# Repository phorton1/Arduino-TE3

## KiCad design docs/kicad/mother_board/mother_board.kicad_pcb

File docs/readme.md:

## TE3 - teensyExpression3

### Please see the [teensyExpression3 documentation](https://phorton1.github.io/Arduino-TE3/)

### License

This program is free software: you can redistribute it and/or modify
it under the terms of the GNU General Public License Version 3 as published by
the Free Software Foundation.

This program is distributed in the hope that it will be useful,
but WITHOUT ANY WARRANTY; without even the implied warranty of
MERCHANTABILITY or FITNESS FOR A PARTICULAR PURPOSE.  See the
GNU General Public License for more details.

Please see **LICENSE.TXT** for more information.

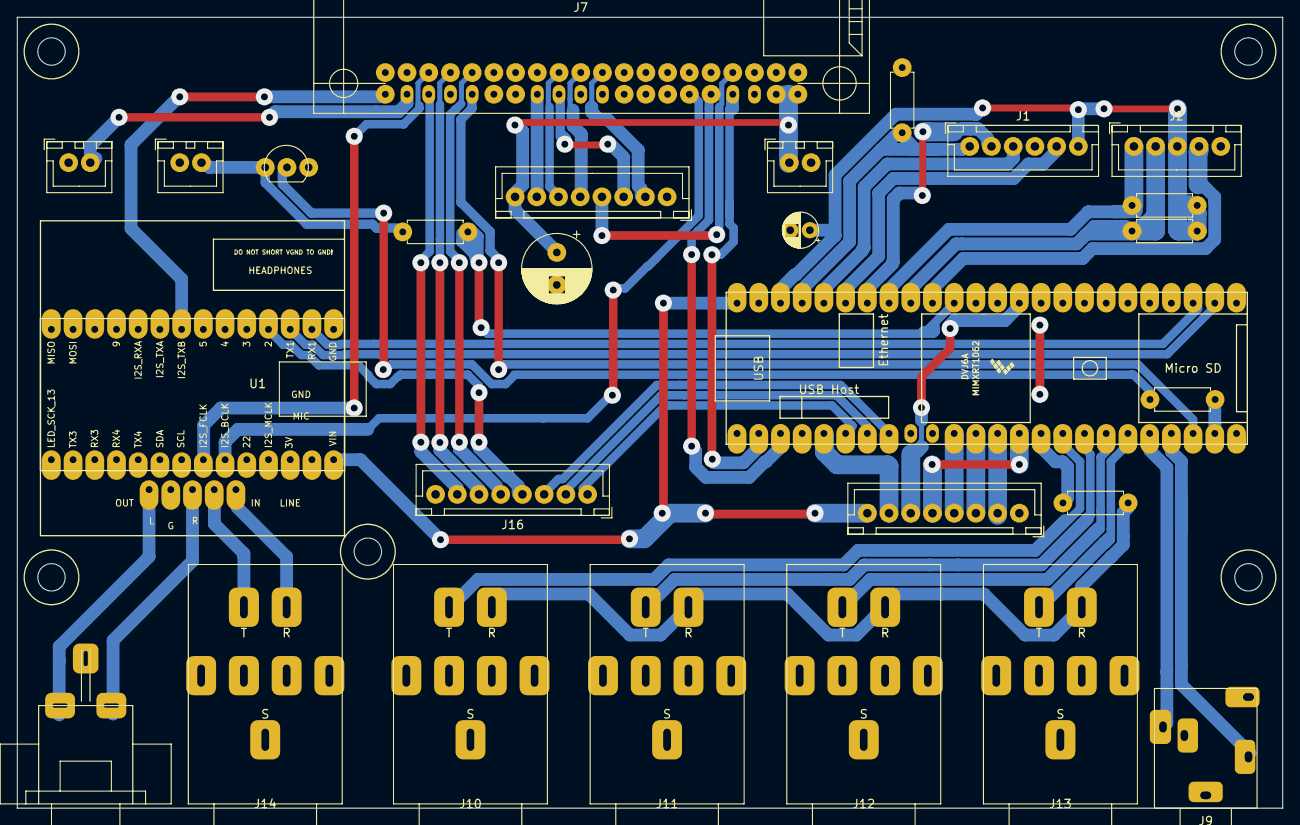
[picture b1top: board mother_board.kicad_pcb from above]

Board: 2 copper layers, 148.0 x 92.5 mm, 27 parts (0 on the bottom side), 54 nets.

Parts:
C1: 100uf; CP_my100uf
C2: 47uf; CP_my10uf
J1: ROW_BOARDS; myJSTx06
J2: ROTARIES; myJSTx05
J3: TE_DISPLAY; myJSTx08
J4: RPI_DISPLAY; myJSTx08
J5: rPi_5V; myJSTx02
J6: RPI_RUN; myJSTx02
J7: rpi_connector; rpi_zero_2w_for_TE3
J8: I2S_TXB; myJSTx02
J9: EigthInchJack1
J10: PEDAL1; QuarterInchJack1
J11: PEDAL2; QuarterInchJack1
J12: PEDAL3; QuarterInchJack1
J13: PEDAL4; QuarterInchJack1
J14: GUITAR_IN; QuarterInchJack1
J15: LINE_OUT; RCA2_PCB_milled
J16: LEDS; myJSTx08
Q1: BC547; myTransistor
R1, R2, R4: 1K; myResistor
R3, R5: 220; myResistor
R11: 10K; myResistor
U1: teensyAudioRevD_WithAudio; audioShieldRevD_audioPinsStack
U2: myTeensy4.1; teensy41

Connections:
+5V: J3.8, U1.28, U2.48
BTN_CLK: J1.5, U2.43
BTN_DIN: J1.3, U2.44
BTN_SENSE: J1.1, R11.1, U2.45
GND: C1.2, C2.2, J1.4, J2.5, J3.1, J4.1, J5.2, J6.1, J7.6, J7.9, J7.14, J7.20, J7.25, J7.30, J7.34, J7.39, J8.1, J9.S, J10.S, J11.S, J12.S, J13.S, J14.S, J15.G, J16.8, Q1.3, R11.2, U1.1, U1.27, U1.32, U2.1, U2.34, U2.47
I2S_BCLK: J7.12, U1.23
I2S_FCLK: J7.35, U1.22
I2S_RXB: J7.40, U1.8
I2S_TXB: J7.38, J8.2
LED_AUDIO_BUSY: J16.4, U1.4
LED_DIN: J1.2, U2.42
LED_RPI_BUSY: J7.31, J16.5
LED_RPI_I2S_RX: J7.33, J16.6
LED_RPI_I2S_TX: J7.36, J16.7
LED_RPI_READY: J16.3, U2.8
LED_RPI_RUN: J16.2, U2.7
LED_T3_BUSY: J16.1, U2.6
LINE_IN_L: J14.R, U1.29
LINE_IN_R: J14.T, U1.30
LINE_OUT_L: J15.L, U1.33
LINE_OUT_R: J15.R, U1.31
unnamed: J10.R, J11.R, J12.R, J13.R, R5.2
unnamed: Q1.2, R4.2
PEDAL1: J10.T, U2.16
PEDAL2: J11.T, U2.17
PEDAL3: J12.T, U2.18
PEDAL4: J13.T, U2.19
PI_REBOOT: R4.1, U2.23
ROT_INT: J2.4, U2.39
RPI_5V: C1.1, J4.8, J5.1, J7.2, J7.4
RPI_LCD_CS: J4.3, J7.24
RPI_LCD_DC: J4.4, J7.7
RPI_MISO: J4.5, J7.21
RPI_MOSI: J4.2, J7.19
RPI_READY: J7.32, U2.22
RPI_RUN: J6.2, Q1.1, R3.2
RPI_SCLK: J4.6, J7.23
RPI_T_CS: J4.7, J7.26
SENS_PI_RUN: R3.1, U2.38
T41_3V3: C2.1, J1.6, J2.3, R1.1, R2.1, R5.1, U2.15, U2.46
T41_LCD_CS: J3.3, U2.12
T41_LCD_DC: J3.4, U2.11
T41_MISO: J3.5, U2.14
T41_MOSI: J3.2, U2.13
T41_RX1: J7.8, U2.2
T41_RX7: J9.T, U2.21
T41_RX8: U1.3, U2.26
T41_SCL: J2.1, R1.2, U2.41
T41_SCLK: J3.6, U2.35
T41_SDA: J2.2, R2.2, U2.40
T41_TX1: J7.10, U2.3
T41_TX7: J9.R, U2.20
T41_TX8: U1.2, U2.27
T41_T_CS: J3.7, U2.5

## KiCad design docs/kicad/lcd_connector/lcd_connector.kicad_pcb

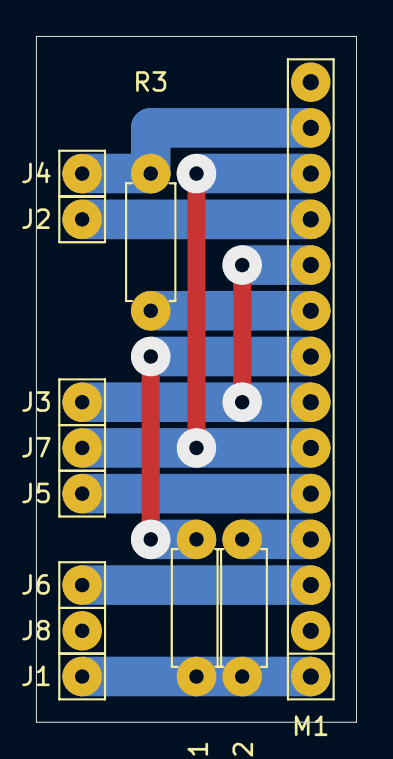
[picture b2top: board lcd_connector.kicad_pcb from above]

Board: 2 copper layers, 17.8 x 38.1 mm, 12 parts (0 on the bottom side), 11 nets.

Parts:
J1: 5V; my1pin
J2: T_CS; my1pin
J3: CLK; my1pin
J4: MISO; my1pin
J5: DC; my1pin
J6: CS; my1pin
J7: MOSI; my1pin
J8: GND; my1pin
M1: TFT_ILI9488; myPinSocket_1x14
R1: 100; myResistor
R2: 10K; myResistor
R3: 220; myResistor

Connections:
unnamed: J1.1, M1.1, R1.1, R2.1
unnamed: J2.1, M1.11
unnamed: J3.1, M1.7, M1.10
unnamed: J4.1, M1.13, R3.1
unnamed: J5.1, M1.5
unnamed: J6.1, M1.3
unnamed: J7.1, M1.6, M1.12
unnamed: J8.1, M1.2
unnamed: M1.4, R2.2
unnamed: M1.8, R1.2
unnamed: M1.9, R3.2

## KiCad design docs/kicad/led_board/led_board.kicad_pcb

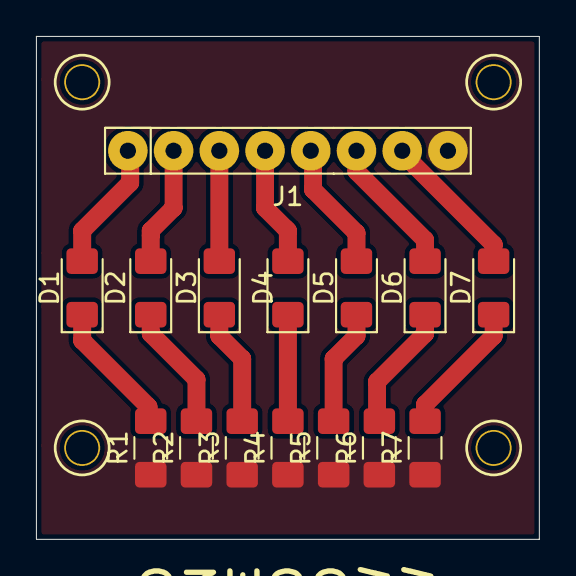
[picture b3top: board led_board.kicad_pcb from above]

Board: 2 copper layers, 27.9 x 27.9 mm, 15 parts (0 on the bottom side), 15 nets.

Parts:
D1, D2, D3, D4, D5, D6, D7: LED_Small; D_1206_3216Metric_Pad1.42x1.75mm_HandSolder
J1: Conn_01x08; my8Pin
R1, R2, R3, R4, R5, R6, R7: R_Small; R_1206_3216Metric_Pad1.42x1.75mm_HandSolder

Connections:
GND: J1.8, R1.1, R2.1, R3.1, R4.1, R5.1, R6.1, R7.1
unnamed: D1.1, R1.2
unnamed: D1.2, J1.1
unnamed: D2.1, R2.2
unnamed: D2.2, J1.2
unnamed: D3.1, R3.2
unnamed: D3.2, J1.3
unnamed: D4.1, R4.2
unnamed: D4.2, J1.4
unnamed: D5.1, R5.2
unnamed: D5.2, J1.5
unnamed: D6.1, R6.2
unnamed: D6.2, J1.6
unnamed: D7.1, R7.2
unnamed: D7.2, J1.7

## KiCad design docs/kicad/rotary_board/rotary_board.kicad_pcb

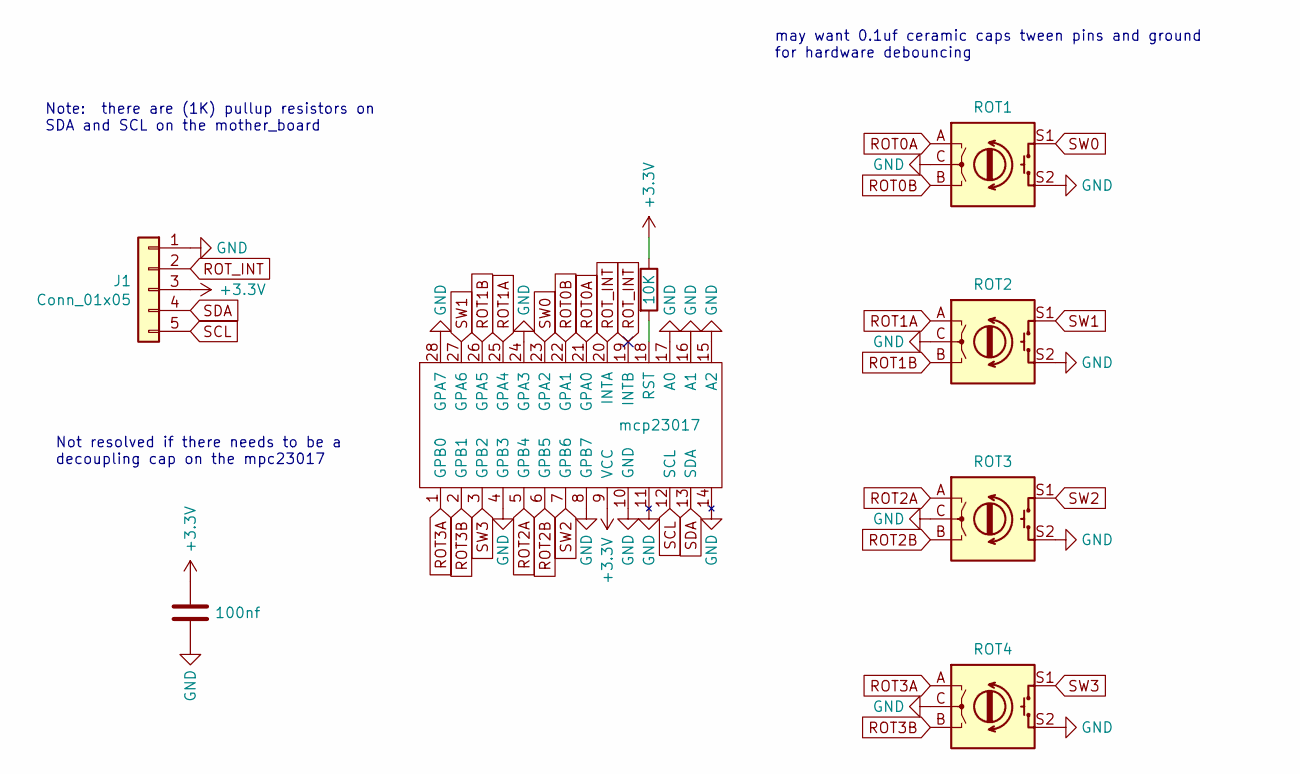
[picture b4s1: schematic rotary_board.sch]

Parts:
C1: 100nf; myCapCeramicSmall
J1: Conn_01x05; my5Pin
R1: 10K; myResistor
SW1: ROT1; myRotaryEncoder
SW2: ROT2; myRotaryEncoder
SW3: ROT3; myRotaryEncoder
SW4: ROT4; myRotaryEncoder
U1: mcp23017; myDip28

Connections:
+3V3: C1.1, J1.3, R1.1, U1.9 (VCC)
GND: C1.2, J1.1, SW1.C, SW1.S2, SW2.C, SW2.S2, SW3.C, SW3.S2, SW4.C, SW4.S2, U1.4 (GPB3), U1.8 (GPB7), U1.10 (GND), U1.11, U1.14, U1.15 (A2), U1.16 (A1), U1.17 (A0), U1.24 (GPA3), U1.28 (GPA7)
unnamed: R1.2, U1.18 (RST)
ROT0A: SW1.A, U1.21 (GPA0)
ROT0B: SW1.B, U1.22 (GPA1)
ROT1A: SW2.A, U1.25 (GPA4)
ROT1B: SW2.B, U1.26 (GPA5)
ROT2A: SW3.A, U1.5 (GPB4)
ROT2B: SW3.B, U1.6 (GPB5)
ROT3A: SW4.A, U1.1 (GPB0)
ROT3B: SW4.B, U1.2 (GPB1)
ROT_INT: J1.2, U1.19 (INTB), U1.20 (INTA)
SCL: J1.5, U1.12 (SCL)
SDA: J1.4, U1.13 (SDA)
SW0: SW1.S1, U1.23 (GPA2)
SW1: SW2.S1, U1.27 (GPA6)
SW2: SW3.S1, U1.7 (GPB6)
SW3: SW4.S1, U1.3 (GPB2)

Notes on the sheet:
Note: there are (1K) pullup resistors on SDA and SCL on the mother_board
Not resolved if there needs to be a decoupling cap on the mpc23017
may want 0.1uf ceramic caps tween pins and ground for hardware debouncing

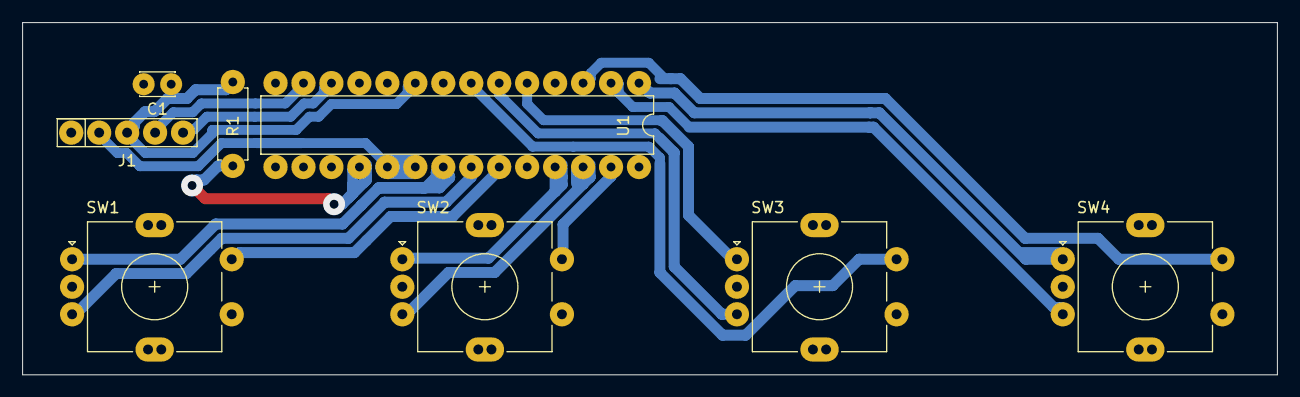
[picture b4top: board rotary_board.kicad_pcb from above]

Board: 2 copper layers, 114.0 x 32.0 mm, 8 parts (0 on the bottom side), 18 nets.

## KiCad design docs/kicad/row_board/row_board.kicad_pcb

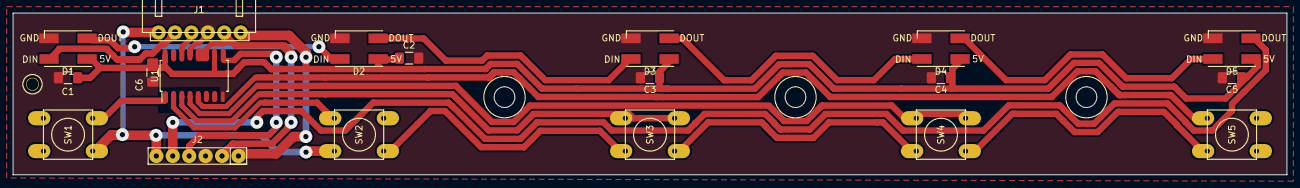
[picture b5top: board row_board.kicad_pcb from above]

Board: 2 copper layers, 197.0 x 25.0 mm, 19 parts (0 on the bottom side), 17 nets.

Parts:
C1, C2, C3, C4, C5: 100nf; C_1206_3216Metric_Pad1.42x1.75mm_HandSolder
C6: 10uf; C_1206_3216Metric_Pad1.42x1.75mm_HandSolder
D1, D2, D3, D4, D5: WS2812B; myWS2812
J1: Conn_01x06; invRightAngleJSTx06
J2: Conn_01x06; my6Pin-08mm
SW1, SW2, SW3, SW4, SW5: SW1; mySwitchSoft
U1: 74HC595; SOIC-16_4.55x10.3mm_P1.27mm

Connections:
+5V: C1.1, C2.1, C3.1, C4.1, C5.1, C6.1, D1.1, D2.1, D3.1, D4.1, D5.1, J1.6, J2.1, U1.10, U1.16
BTN_CLK: J1.5, J2.2, U1.11, U1.12
BTN_DIN: J1.3, U1.14
BTN_DOUT: J2.4, U1.9
BTN_SENSE: J1.1, J2.6, SW1.2, SW2.2, SW3.2, SW4.2, SW5.2
GND: C1.2, C2.2, C3.2, C4.2, C5.2, C6.2, D1.3, D2.3, D3.3, D4.3, D5.3, J1.4, J2.3, U1.8, U1.13
LED_DIN: D1.4, J1.2
LED_DOUT: D5.2, J2.5
unnamed: D1.2, D2.4
unnamed: D2.2, D3.4
unnamed: D3.2, D4.4
unnamed: D4.2, D5.4
unnamed: SW1.1, U1.1
unnamed: SW2.1, U1.2
unnamed: SW3.1, U1.3
unnamed: SW4.1, U1.4
unnamed: SW5.1, U1.5

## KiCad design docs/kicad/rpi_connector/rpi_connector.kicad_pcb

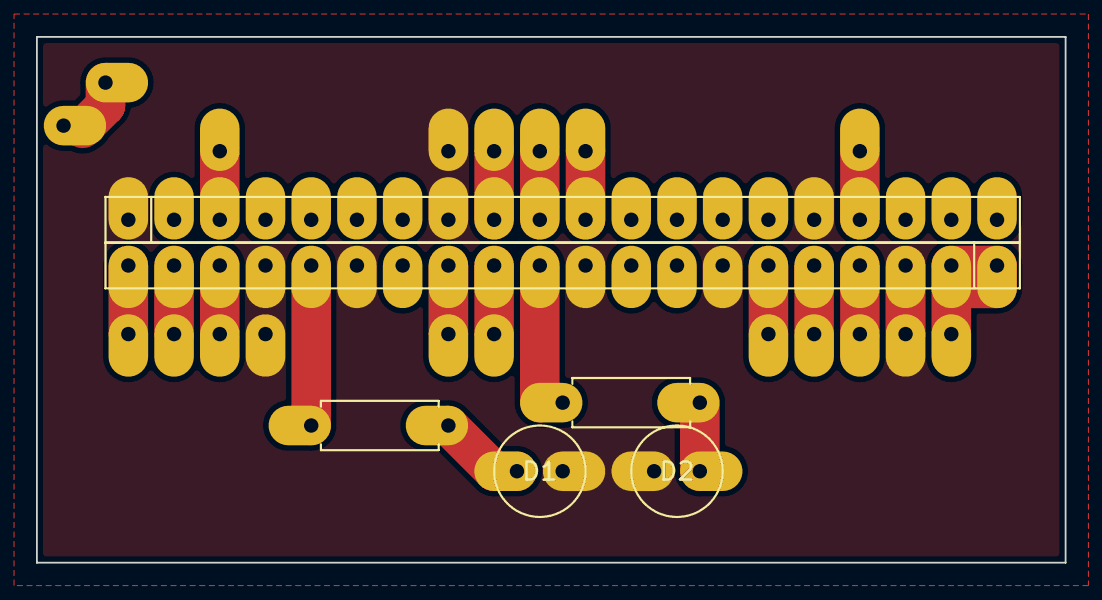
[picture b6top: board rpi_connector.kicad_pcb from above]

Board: 2 copper layers, 57.2 x 29.2 mm, 7 parts (0 on the bottom side), 6 nets.

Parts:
D1, D2: yellow; led_yellow
J12: RPI_RUN; Oval1Pin
J13: rpiB; pinSocket1x20_bottom
J14: rpiA; pinSocket1x20_bottom
R1, R2: 220; resistor

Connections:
GND: D1.1, D2.1, J13.1, J13.8, J13.16, J14.3, J14.7, J14.10, J14.15, J14.17
unnamed: D1.2, R1.1
unnamed: D2.2, R2.1
RPI_5V: J14.1, J14.2
RPI_I2S_RX_ACTIVE: J14.11, R2.2
RPI_I2S_TX_ACTIVE: J14.16, R1.2

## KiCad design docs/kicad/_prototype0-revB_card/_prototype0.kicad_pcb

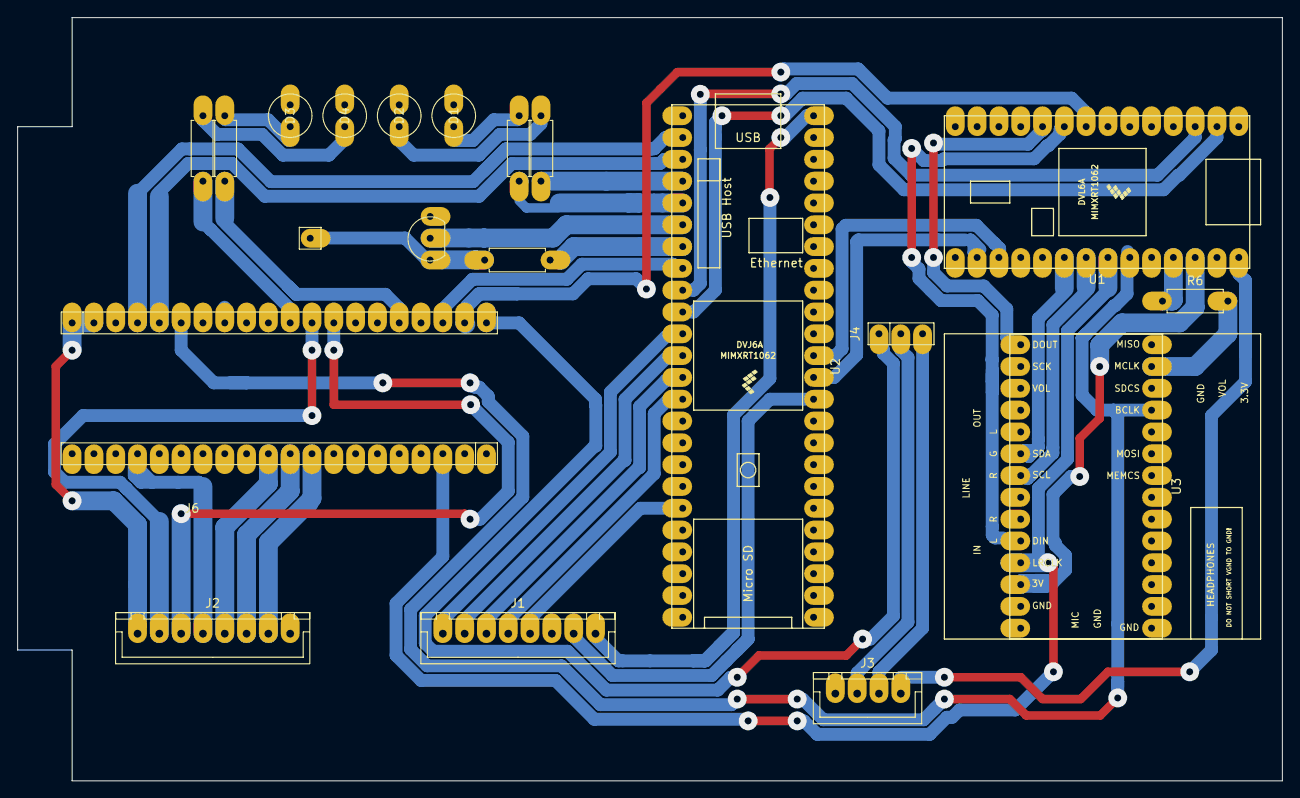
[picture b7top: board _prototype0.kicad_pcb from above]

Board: 2 copper layers, 147.3 x 88.9 mm, 21 parts (0 on the bottom side), 47 nets.

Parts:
D1: GREEN; led_green
D2: BLUE; led_blue
D3, D4: YELLOW; led_yellow
J1: T3_ILI9488; JST8
J2: RPI_ILI9488; JST8
J3: USB Host; JST4
J4: 40 bottom; pinSocket1x3
J5: RPI_RUN; pinSocket1x1
J6: rpiB; pinSocket1x20
J7: rpiA; pinSocket1x20
Q1: BC547; transistor
R1, R3, R4, R5: 220; resistor
R2: 560; resistor
R6: 100; resistor
U1: myTeensy4.0; teensy40
U2: myTeensy4.1; teensy41
U3: teensyAudioRevB; audioShieldRevB

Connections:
GND: D1.1, D2.1, D3.1, D4.1, J1.6, J2.8, J3.1, J6.1, J6.8, J6.16, J7.3, J7.7, J7.10, J7.15, J7.17, Q1.3, U1.1, U1.27, U2.1, U2.34, U2.47, U3.1, U3.27
HOST_D+: J3.2, J4.2
HOST_D-: J3.3, J4.3
I2S_BCLK: J7.6, U1.23, U3.11
I2S_FCLK: J6.3, U1.22, U3.25
I2S_MCLK: R6.1, U1.25
I2S_RXA: U1.10, U3.15
I2S_RXB: J4.1, J7.20
I2S_TXA: U1.9, U3.24
I2S_TXB: J7.19, U1.8
LED_PI_READY: R2.1, U2.4
LED_PI_RUN: R1.1, U2.5
unnamed: D1.2, R1.2
unnamed: D2.2, R2.2
unnamed: D3.2, R3.2
unnamed: D4.2, R4.2
unnamed: R6.2, U3.13
PI_REBOOT: Q1.2, U2.6
RPI_5V: J2.1, J7.1, J7.2
RPI_CD: J2.4, J6.17
RPI_I2S_RX_ACTIVE: J7.11, R4.1
RPI_I2S_TX_ACTIVE: J7.16, R3.1
RPI_LED_CS: J2.2, J7.12
RPI_MISO: J2.6, J6.10
RPI_MOSI: J2.5, J6.11
RPI_READY: J7.18, U2.8
RPI_RUN: J5.1, Q1.1, R5.2
RPI_RX: J7.5, U2.3
RPI_SCLK: J2.7, J6.9
RPI_TOUCH_CS: J2.3, J7.13
RPI_TX: J7.4, U2.2
SENS_PI_RUN: R5.1, U2.7
T40_3.3V: U1.26, U3.26
T40_5V: J3.4, U1.28
T40_RX1: U1.2, U2.10
T40_RX3: U1.17, U2.37
T40_SCA: U1.20, U3.20
T40_SCL: U1.21, U3.21
T40_TX1: U1.3, U2.9
T40_TX3: U1.16, U2.36
T41_5V: J1.8, U2.48
T41_CD: J1.1, U2.11
T41_LED_CS: J1.2, U2.12
T41_MISO: J1.4, U2.14
T41_MOSI: J1.3, U2.13
T41_SCLK: J1.7, U2.35
T41_TOUCH_CS: J1.5, U2.19

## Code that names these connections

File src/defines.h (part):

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
// LEDs

#define PIN_LED_T3_BUSY 	4		// RED LED with 220 ohm resistor
#define PIN_LED_RPI_RUN		5		// GREEN LED with 100 ohm resistor
#define PIN_LED_RPI_READY	6		// BLUE LED with 220 ohm reisitor

// display (ili9488_t3)

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
// row boards

#define PIN_LED_DIN				20	// only pin on teensy4.x that supports ws3812bSerial
#define PIN_BTN_CLK				21
#define PIN_BTN_DIN				22
#define PIN_BTN_SENSE			23

// pedals
// the pin numbers in the schematic are currently backwards
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
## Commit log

2024-05-10 corrected link to phorton1/vGuitar/vGuitar.md
2024-05-11 iniitial TE3.ino and rotaryBoard.h & cpp & schematic tested as prototype
2024-05-11 added .gitignore to all TE related doc/kicad folders. Renamed and moved kicad designs around. See /junk/maybe_save for remnants
2024-05-12 updated kicad .gitignore's
2024-05-13 update all TE preferences.txt to build in /src/ArduinoBuilds for easier clean builds
2024-05-13 added ESP32 initial version of WITH_HUB_SERIAL and esp32_breadboard kicad stuff
2024-05-14 moved TE3 and TE3_hub implementation files to /src
2024-05-15 added Arduino-libraries-TE3_common repo, starting with (renamed) teSGTL5000.h and cpp
2024-05-19 change back to fast upload speed
2024-05-19 cleanup; breakout serial.h and cpp, write testSerialImplementation that lets me telnet to ESP32 to control the teensy SGTL5000
2024-05-19 added telnetTask and queue from TE3_hub for performance reasons
2024-05-21 After first tests with iPad USB - reworked TE3_hub audio setup; reworked SGTL5000 setDefaults() and some method semantics; moved sgtl5000 implementation to TE3_hub; made sgtl5000midi.h and teCommon.h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
2024-05-28 pushing intermediate and messy TE3 vGuitar system kicad designs
2024-05-31 added a square wave signal generator to test opto isolation
2024-08-12 junk TE docs
2025-01-22 restart TE3 project - BEFORE CHANGING TE3 TO TEENSY 4.1 - LAST ESP32 TE3 version
2025-01-23 INITIAL COMMIT OF "REAL" TEENSY 4.1 based TE3
2025-01-23 TE3 & TE_HUB - add/cleanup USB descdriptors; move midiHost from TE_HUB to TE3
2025-01-23 got rid of (many) vestigial TE3 design attempts; consolidating electronics under TE3/docs/kicad
2025-01-24 got rid of obsolete docs in prep for TE3 actual design
2025-01-24 renamed TE3_hub to TE3_audio
2025-01-24 added kicad lcd_connector to TE3 repo
2025-01-24 initial kicad design of TE3 mother_board
2025-01-25 tested prototype rotary board
2025-01-27 built row_board_prototype pcb; added te3_leds (with BC547 level up shifter) and prep for te3_buttons (with 74HC595 polling)
2025-01-27 implemented code for and tested row_board_prototype
2025-01-30 implemented & tested 2nd row_board prototype 595 buttons; switch to 3.3V row_boards; got rid of 1st row board prototype kicad; ready to start designing motherboard
2025-01-30 call setUSBSerialNumber() from _usb.c and show it in INO programs (with addl comments)
2025-01-30 cleanup comments; remove vestigial 595 code
2025-01-30 mother_board schematic comments only
2025-01-31 update teensy Arduino preferences.txt to work on USBC hub
2025-02-02 add BUSY (as well as current ALIVE) LEDa
2025-02-02 continuing work on TE3 kicad designs
2025-02-06 added some test code to send out a midi message (guitar distortion on/off) within the prototype/breadboard system
2025-02-06 FINALLY landed on the store bought USBC hub solution. It works in any cable orientation and charges the iPad at 15V/25W while also working with USB midi, and presumably audio, data. - remove glue and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
2025-02-06 YAY! Ready to start designing actual mother_board and USBC_connector boards, to move on to 3D printing stuff
2025-02-07 design TE3 motherboard
2025-02-07 mod TE3 pins accoring to mother_board design (reworked breadboard)
2025-02-09 new row board design (with chip at left end)
2025-02-09 messing with kicad and flatcam - gonna upgrade to kicad 8
2025-02-11 kicad changes to support actual Fusion 360 TE3 design efforts - created rotary board PCB
2025-02-14 added kicad led_board, updated mother board RCA socket
2025-02-25 printed first 3D parts for TE3
2025-02-25 cutting actual TE3 milled circuit boards
2025-02-27 3D print most of TE3
2025-02-27 PCB milling marathon - made 5 row_boards, rotary_board, led_board, and reworked detailed design of motherboard - motherboard *should* match old one that was milled and installed in initial TE3 box
2025-03-05 got rid of obsolete old mother_board and row_board kicad files
2025-03-05 added TE3 milled USBA connector with 3D printed case
2025-03-05 added TE3 lcd_connector kicad_pcb, though I'm using ones milled a long time ago for cnc20mm
2025-03-05 final inital TE3 3D printing
2025-03-05 final initial TE3 PCBS - updated LED board green resistor to 1K - changed TE3 display SCLK to pin13 as it is required for hardware SPI0 - changed nomenclature of rotary board to ROT0..ROT4 and correc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
2025-03-05 started rewrite of TE3 docs and added temporary todo.txt
2025-03-05 fixed WS2812b led ordering as they are now all left-to-right on row_boards instead of alternating left-to-right then right-to-left as in TE1/2
2025-03-05 TE3 PCB UNIT TESTS - rotary board, and row_board testing - added raw button presses to rotaryBoard.h/cpp and fixed inverted rotary 3/4 order as per PCB - added initial crude te3_tft.h and cpp to veri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
2025-03-05 START INTEGRATED TE3 mother_board testing - got the rPi display and com port basically working - discovered I had left the circle stuff in odd shape (460800 using OCTO audio device even with LOOPER3 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
2025-03-05 Fixed problems discovered after milling 1st test mother_board. - effing had I2S BCLK and FCLK going to wrong pins on teensy4.0!! - connector for revD audio pins was off by 1.5mm - separated rPI and t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
2025-03-05 added Looper commonDefines.h to TE3 project
2025-03-05 completed first phase of mother_board testing ... - implemented rPi state LEDs - got rid of PIN_LED_TE3_ALIVE which conflicted with needed use of teensy4.1 pin13 as SCLK for display - implemented rud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
2025-03-05 added important 220 ohm resistor with MISO going FIRST to Touch after TE3 testing
2025-03-06 final integration test before adding audio connectors, hot gluing wires, and cutting wood base - tested with usbC hub, deleted all COM and TE3 related devices so TE3 is now COM3 and TE3_audio is COM4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
2025-03-06 check in fusion stuff and base lightburn
2025-03-07 loosen slider tolerances and fix host usb bracket in fusion design, stl's, and prusa projects and gcode files after initial print/assembly
2025-03-07 initial test of pedals
2025-03-07 got rid of temporary todo.txt
2025-03-07 INITIAL ROUGH PORT OF TE1 --> TE3 (without fileSystem stuff) - boots and somewhat sort of works
2025-03-07 had to subclass ILI9488_t3 and jump through hoops just to getCharWidth() in pixels
2025-03-07 continuing shotgun port of TE1 - added individual debug output prefs
2025-03-08 added "data" folder (songs) from TE1 to TE3
2025-03-08 implemented variable serial TEXT ouitput and got FTP up for first time with midiOx and via the midiHost
2025-03-09 Iniitial BREAKTHROUGH implementation of fileSystem basics - uses fileXXXX.h and cpp common to TE1, TE2, and TE3 - TE1/2 now use official teensy SD/SdFat libraries! - so can get rid of my old denormal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
2025-03-09 remove bogus nested /data/songs/data files
2025-03-09 INITIAL crude WORKING FILE SERVER; fileXXX.h and cpp need normalization to TE1/2 - moved timer_handler() loop methods to TE3.ino loop() method - got rid of all FULL_IMPLEMENTATION 0 defines - minor f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
2025-03-09 made bug fixes to get default font to work in ILI9488_t3 for TE3
2025-03-09 Got winSelectSong to open and at least display a songmachine file
2025-03-10 check for null TE3_DEBUG_STREAM before using it
2025-03-10 fixed multi-line printJustified calls; added DEBUG_PRINT_JUST define
2025-03-10 smaller boot delay
2025-03-10 added songMachine debugging and got BIG_RIVER and CHINA_CAT running correctly
2025-03-10 increase ctrl-E timeout window for binary uploads over TE3 DBG_SERIAL_PORT. addl - te3_serial: don't output to mappable RPI and HUB output devices if they are zero;
2025-03-11 found, documented, and fixed test PCB problems with I2S_IXR, LINE_IN_R, GND, and LINE_OUT_R traces (bad schematic and bad kicad symbols)
2025-03-11 check in TE3, TE3_audo, circle/_prh, and _apps/Looper after initial TE3 integration success. - rotaries don't work - only very few USBC cables work on the iPad, but strangely those that do, also work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
2025-03-12 TURNED on rotary debugging and comments only
2025-03-12 BEGIN MIDI PORT REWORK - brought midiQueue.h/cpp and ftp.h/cpp from TE2, renamed existing TE3's to avoid conflicts
2025-03-13 REWORKED ENTIRE MIDI_PORT SCHEME - including defines, prefs, options, midiQueue, midiHost, and ftp.cpp and h - requires myDebug fixes to fix "rotaries not working or crashing" bug. - tested on desk w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
2025-03-13 IMPLEMENTED INITIAL TE3 MIDI_MONITOR; VERFIED ROTARIES NOW WORK - moved msgUnion from TE3 midiQueue.h to TE_Common/teMIDI.h - eliminated MIDI_CABLE stuff and got TE3_audio working with that change - 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
2025-03-14 Implement Looper specific CC Monitoring; TE3.ino now issues LOOP_COMMAND_GET_STATE at RPI_READY and responds to LOOP_CONTROL VOLUMES - volumes get set so that rotaries don't jump - turn off dbgSerial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
2025-03-15 change TE3 and TE3_audio preferences to compile via hub into LEFT plug on laptop
2025-03-15 more fruitless playing with the USBC hub cable issue
2025-03-15 fix pedal output channel
2025-03-15 fix setFTPActivePort and switch from MIDI_PORT_USB1 (0x00) to MIDI_PORT_USB2 (0x01) for remote ftp
2025-03-15 Implement te3_serial.cpp circular buffers, separating pollSerial(), called by timer_handler() from processSerial(), called by loop() - cleanup te3_sereial.cpp comments and file structure
2025-03-15 important: FIXED te3_serial.cpp "in_file_command" mode to use circular buffer methods; also: - added te3_serial.cpp initSerialBuffers() to malloc() serial buffers rather than use static allocation - 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
2025-03-17 initial stab at NEW HTML DOC STRUCTURE with simple SPA (Single Page Application) to manage content .HTM files
2025-03-18 minor solder.htm documentation fixes
2025-03-18 add readme.md pointing to github pages https://phorton1.github.io/Arduino-TE3/
2025-03-18 minor fix to readme.md
2025-03-18 nuther readme.md update
2025-03-18 add some doc pages
2025-03-18 produced and submitted mother_board and row_board to PCBWay for production
2025-03-19 updated PCBWay designs after DRC Design Rules Checks
2025-03-20 fix large image urls
2025-03-20 fix image urls
2025-03-20 added 1st rough main TE3 and overview images;; minor changes to existing pages
2025-03-21 added "Next" buttons and updated styles
2025-03-22 add 3d printed button caps
2025-03-22 added WITH_SPLASH_SCREEN define for cover photo
2025-03-22 flesh out build.htm page with animations
2025-03-23 added doc link back to main repo
2025-03-23 updated overview drawing
2025-03-23 docs: added target="_blank" to all external links
2025-03-23 docs: added 3dp.htm page
2025-03-23 docs: fix a few typos before showing it to a good friend
2025-03-24 docs: solder.htm typos
2025-03-25 print new fan1_ring1 for stbd fan
